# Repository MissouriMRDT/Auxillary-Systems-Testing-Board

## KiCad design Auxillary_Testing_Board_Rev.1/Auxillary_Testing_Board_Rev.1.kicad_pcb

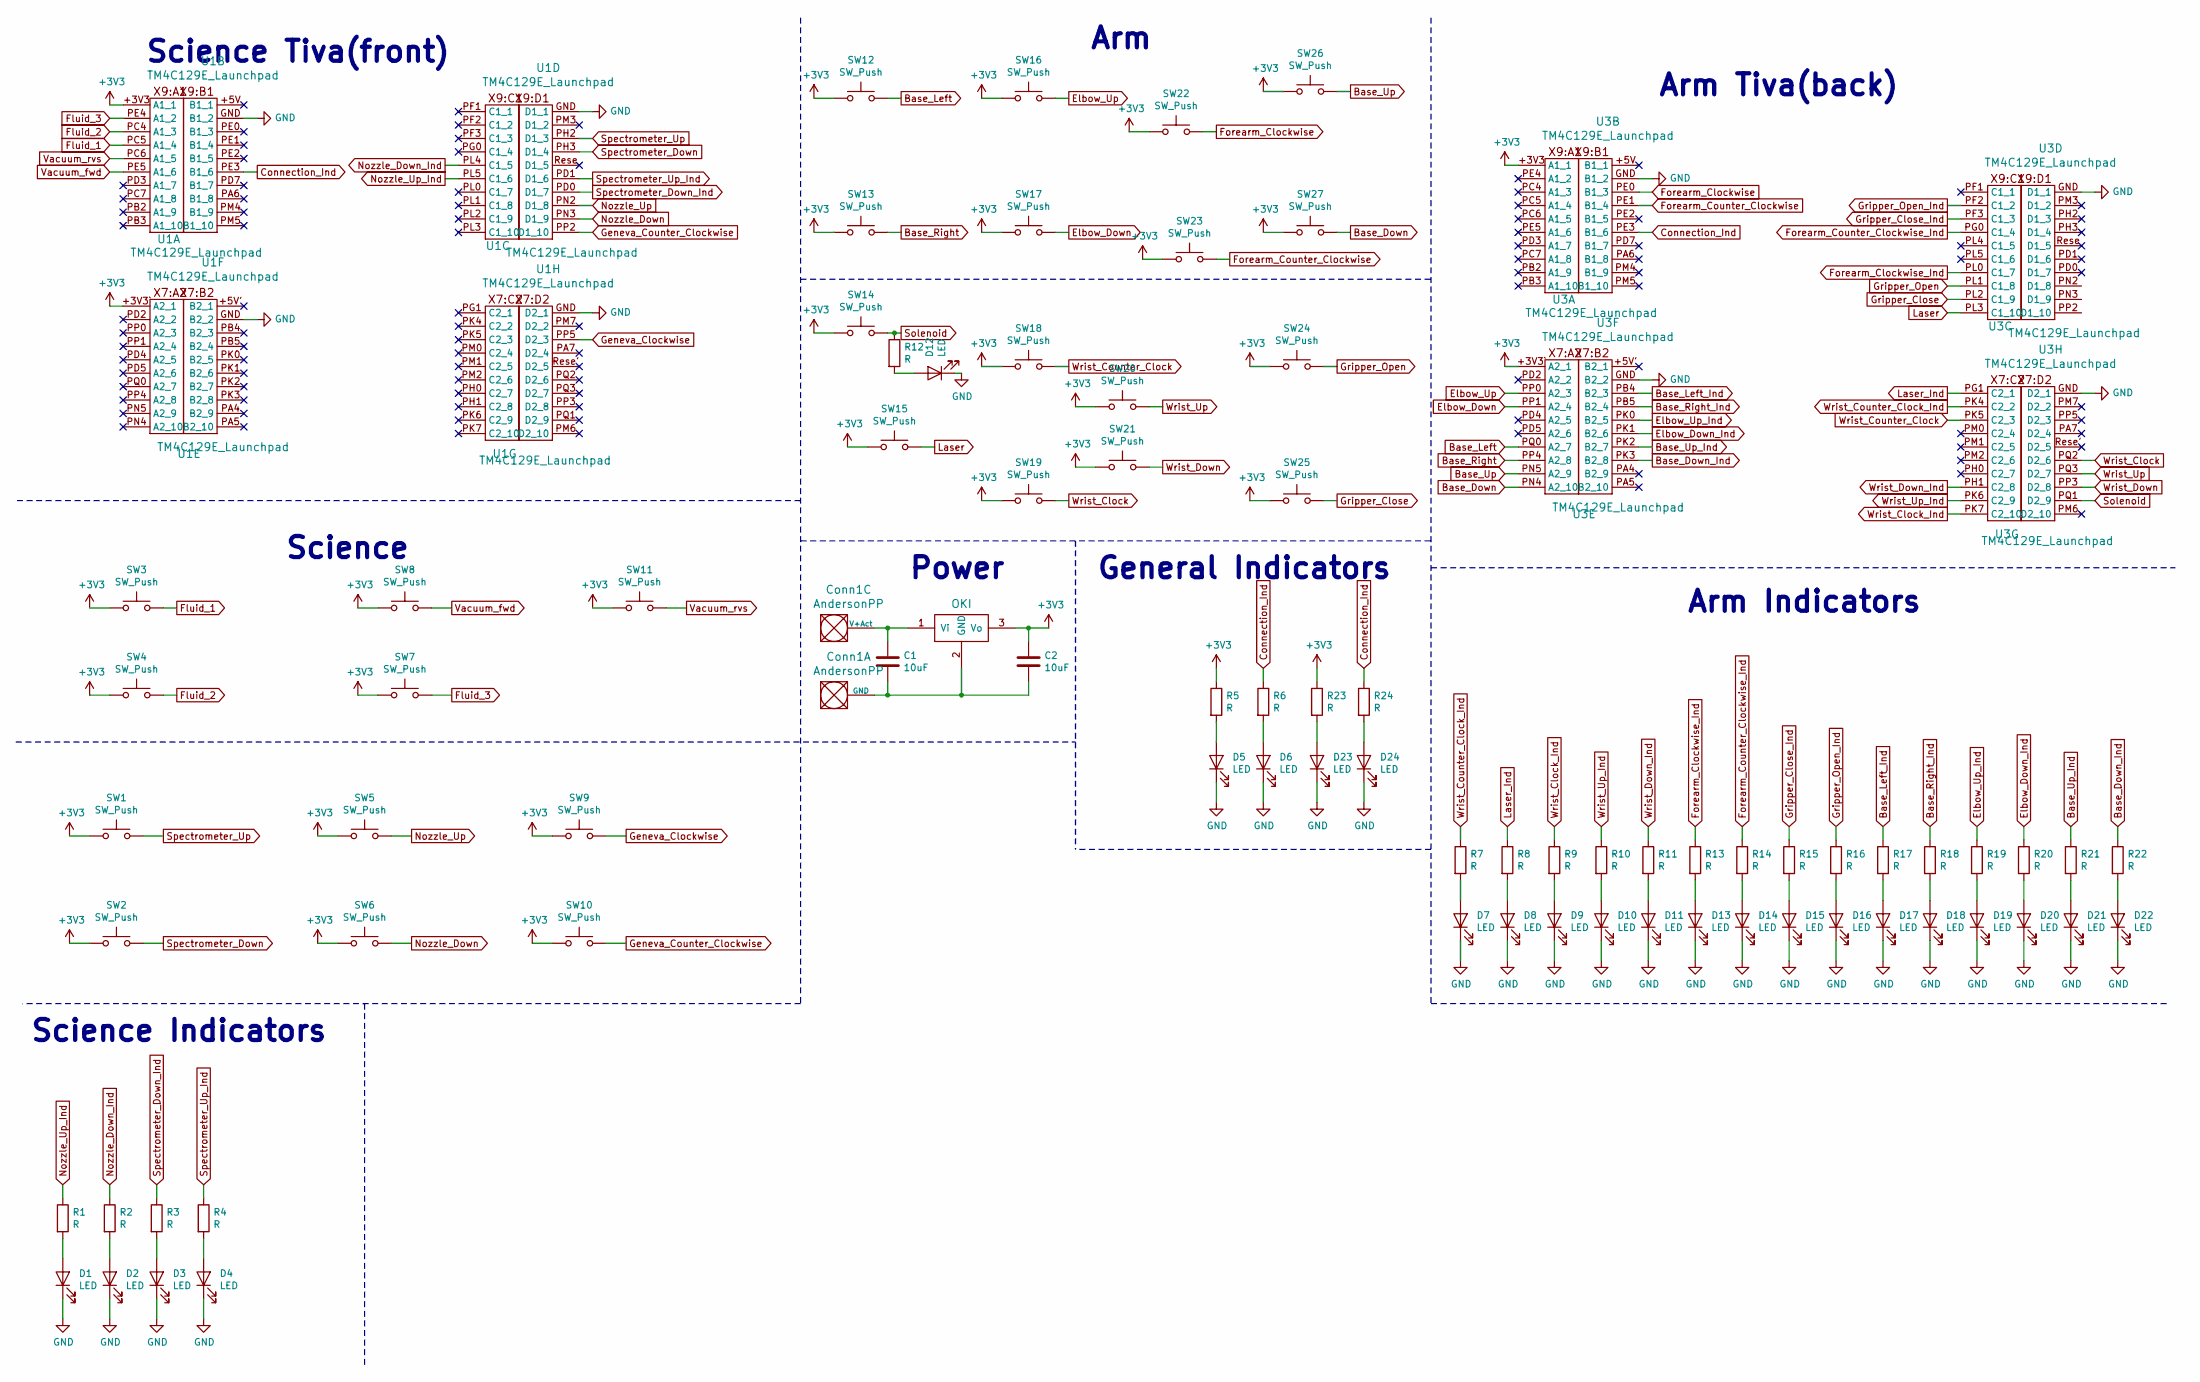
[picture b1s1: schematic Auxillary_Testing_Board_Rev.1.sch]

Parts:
C1, C2: 10uF; C_0603_1608Metric_Pad1.05x0.95mm_HandSolder
Conn1: AndersonPP; Anderson_2_Horizontal_Side_by_Side
D1, D2, D3, D4, D5, D6, D7, D8, D9, D10, D11, D12, D13, D14, D15, D16, D17, D18, D19, D20, D21, D22, D23, D24: LED; LED_0603_1608Metric_Pad1.05x0.95mm_HandSolder
R1, R2, R3, R4, R5, R6, R7, R8, R9, R10, R11, R12, R13, R14, R15, R16, R17, R18, R19, R20, R21, R22, R23, R24: R; R_0603_1608Metric_Pad1.05x0.95mm_HandSolder
SW1, SW2, SW3, SW4, SW5, SW6, SW7, SW8, SW9, SW10, SW11, SW12, SW13, SW14, SW15, SW16, SW17, SW18, SW19, SW20, SW21, SW22, SW23, SW24, SW25, SW26, SW27: SW_Push; SW_SPST_TL3305A
U1, U3: TM4C129E_Launchpad; Auxillary_Testing_Board
U2: OKI; OKI_Horizontal

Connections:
+3V3: C2.1, R5.1, R23.1, SW1.1, SW2.1, SW3.1, SW4.1, SW5.1, SW6.1, SW7.1, SW8.1, SW9.1, SW10.1, SW11.1, SW12.1, SW13.1, SW14.1, SW15.1, SW16.1, SW17.1, SW18.1, SW19.1, SW20.1, SW21.1, SW22.1, SW23.1, SW24.1, SW25.1, SW26.1, SW27.1, U1.+3V3 (A1_1), U1.+3V3', U1.+3V3` (A2_1), U2.3 (Vo), U3.+3V3 (A1_1), U3.+3V3` (A2_1)
Base_Down: SW27.2, U1.PN4 (A2_10), U3.PN4 (A2_10)
Base_Down_Ind: R22.1, U1.PK3 (B2_8), U3.PK3 (B2_8)
Base_Left: SW12.2, U1.PQ0 (A2_7), U3.PQ0 (A2_7)
Base_Left_Ind: R17.1, U1.PB4 (B2_3), U3.PB4 (B2_3)
Base_Right: SW13.2, U1.PP4 (A2_8), U3.PP4 (A2_8)
Base_Right_Ind: R18.1, U1.PB5 (B2_4), U3.PB5 (B2_4)
Base_Up: SW26.2, U1.PN5 (A2_9), U3.PN5 (A2_9)
Base_Up_Ind: R21.1, U1.PK2 (B2_7), U3.PK2 (B2_7)
Connection_Ind: R6.1, R24.1, U1.PE3 (B1_6), U3.PE3 (B1_6)
Elbow_Down: SW17.2, U1.PP1 (A2_4), U3.PP1 (A2_4)
Elbow_Down_Ind: R20.1, U1.PK1 (B2_6), U3.PK1 (B2_6)
Elbow_Up: SW16.2, U1.PP0 (A2_3), U3.PP0 (A2_3)
Elbow_Up_Ind: R19.1, U1.PK0 (B2_5), U3.PK0 (B2_5)
Fluid_1: SW3.2, U1.PC5 (A1_4)
Fluid_2: SW4.2, U1.PC4 (A1_3)
Fluid_3: SW7.2, U1.PE4 (A1_2)
Forearm_Clockwise: SW22.2, U1.PE0 (B1_3), U3.PE0 (B1_3)
Forearm_Clockwise_Ind: R13.1, U1.PL0 (C1_7), U3.PL0 (C1_7)
Forearm_Counter_Clockwise: SW23.2, U1.PE1 (B1_4), U3.PE1 (B1_4)
Forearm_Counter_Clockwise_Ind: R14.1, U1.PG0 (C1_4), U3.PG0 (C1_4)
Geneva_Clockwise: SW9.2, U1.PP5 (D2_3)
Geneva_Counter_Clockwise: SW10.2, U1.PP2 (D1_10)
Gripper_Close: SW25.2, U1.PL2 (C1_9), U3.PL2 (C1_9)
Gripper_Close_Ind: R15.1, U1.PF3 (C1_3), U3.PF3 (C1_3)
Gripper_Open: SW24.2, U1.PL1 (C1_8), U3.PL1 (C1_8)
Gripper_Open_Ind: R16.1, U1.PF2 (C1_2), U3.PF2 (C1_2)
Laser: SW15.2, U1.PL3 (C1_10), U3.PL3 (C1_10)
Laser_Ind: R8.1, U1.PG1 (C2_1), U3.PG1 (C2_1)
unnamed: C1.1, Conn1.2 (V+Log), Conn1.3 (V+Act), U2.1 (Vi)
unnamed: D1.2 (A), R1.2
unnamed: D2.2 (A), R2.2
unnamed: D3.2 (A), R3.2
unnamed: D4.2 (A), R4.2
unnamed: D5.2 (A), R5.2
unnamed: D6.2 (A), R6.2
unnamed: D7.2 (A), R7.2
unnamed: D8.2 (A), R8.2
unnamed: D9.2 (A), R9.2
unnamed: D10.2 (A), R10.2
unnamed: D11.2 (A), R11.2
unnamed: D12.2 (A), R12.2
unnamed: D13.2 (A), R13.2
unnamed: D14.2 (A), R14.2
unnamed: D15.2 (A), R15.2
unnamed: D16.2 (A), R16.2
unnamed: D17.2 (A), R17.2
unnamed: D18.2 (A), R18.2
unnamed: D19.2 (A), R19.2
unnamed: D20.2 (A), R20.2
unnamed: D21.2 (A), R21.2
unnamed: D22.2 (A), R22.2
unnamed: D23.2 (A), R23.2
unnamed: D24.2 (A), R24.2
Nozzle_Down: SW6.2, U1.PN3 (D1_9)
Nozzle_Down_Ind: R2.1, U1.PL4 (C1_5)
Nozzle_Up: SW5.2, U1.PN2 (D1_8)
Nozzle_Up_Ind: R1.1, U1.PL5 (C1_6)
Solenoid: R12.1, SW14.2, U1.PQ1 (D2_9), U3.PQ1 (D2_9)
Spectrometer_Down: SW2.2, U1.PH3 (D1_4)
Spectrometer_Down_Ind: R3.1, U1.PD0 (D1_7)
Spectrometer_Up: SW1.2, U1.PH2 (D1_3)
Spectrometer_Up_Ind: R4.1, U1.PD1 (D1_6)
Vacuum_fwd: SW8.2, U1.PE5 (A1_6)
Vacuum_rvs: SW11.2, U1.PC6 (A1_5)
Wrist_Clock: SW19.2, U1.PQ2 (D2_6), U3.PQ2 (D2_6)
Wrist_Clock_Ind: R9.1, U1.PK7 (C2_10), U3.PK7 (C2_10)
Wrist_Counter_Clock: SW18.2, U1.PK5 (C2_3), U3.PK5 (C2_3)
Wrist_Counter_Clock_Ind: R7.1, U1.PK4 (C2_2), U3.PK4 (C2_2)
Wrist_Down: SW21.2, U1.PP3 (D2_8), U3.PP3 (D2_8)
Wrist_Down_Ind: R11.1, U1.PH1 (C2_8), U3.PH1 (C2_8)
Wrist_Up: SW20.2, U1.PQ3 (D2_7), U3.PQ3 (D2_7)
Wrist_Up_Ind: R10.1, U1.PK6 (C2_9), U3.PK6 (C2_9)

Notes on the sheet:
Arm
Science
Power
Science Tiva(front)
Arm Tiva(back)
Arm Indicators
Science Indicators
General Indicators

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
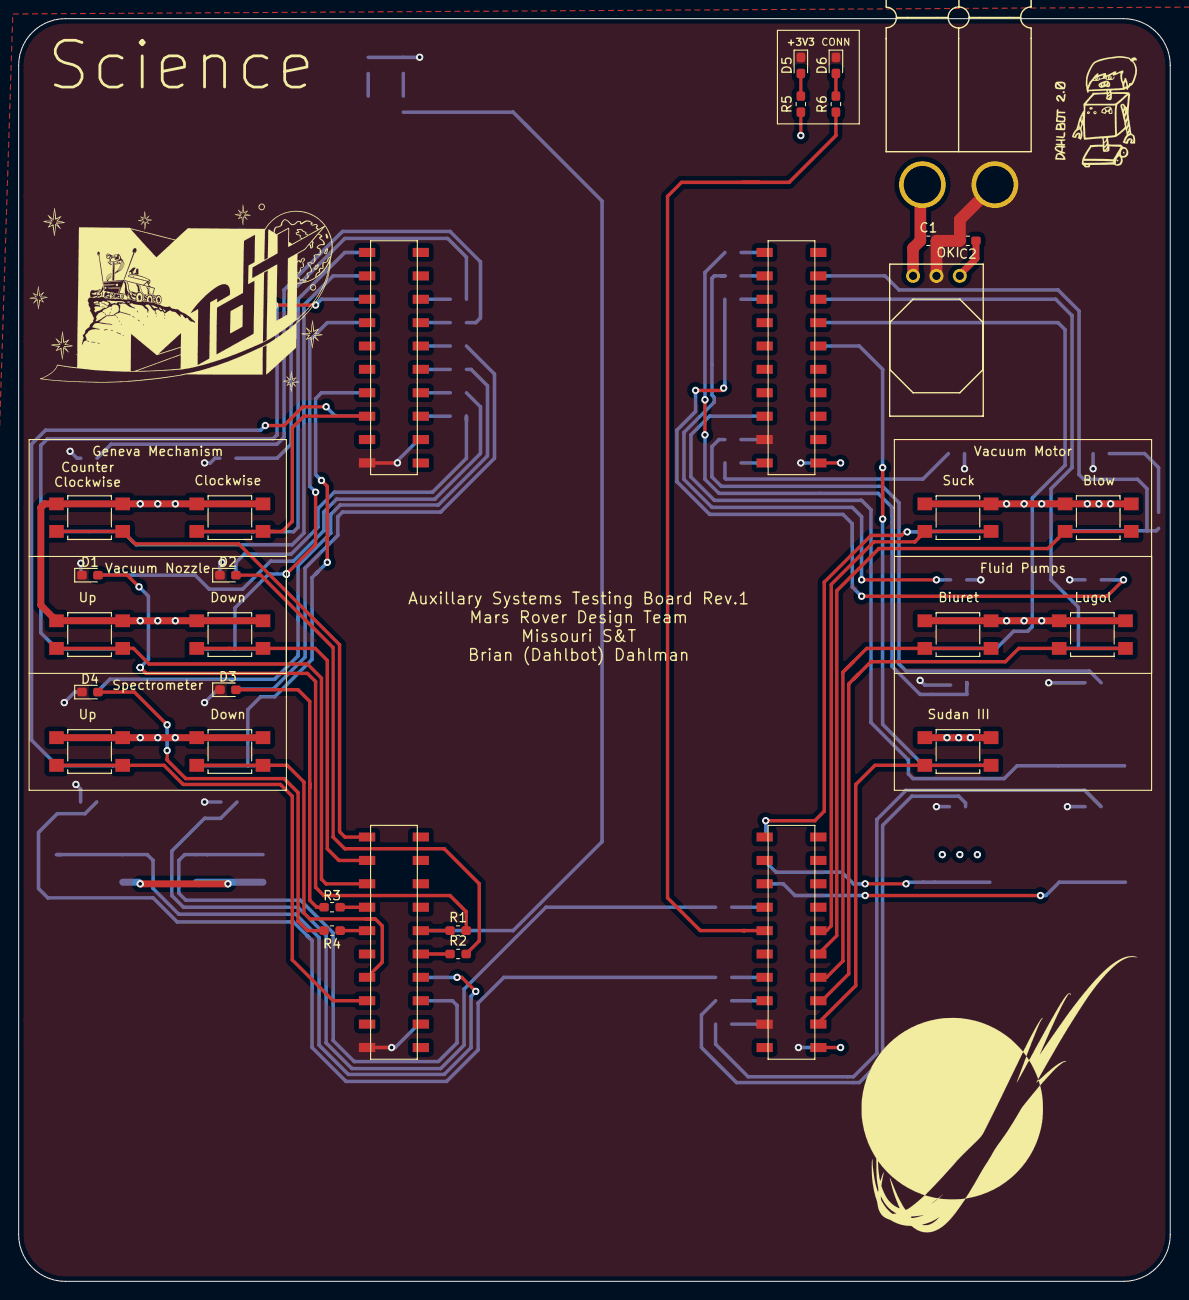
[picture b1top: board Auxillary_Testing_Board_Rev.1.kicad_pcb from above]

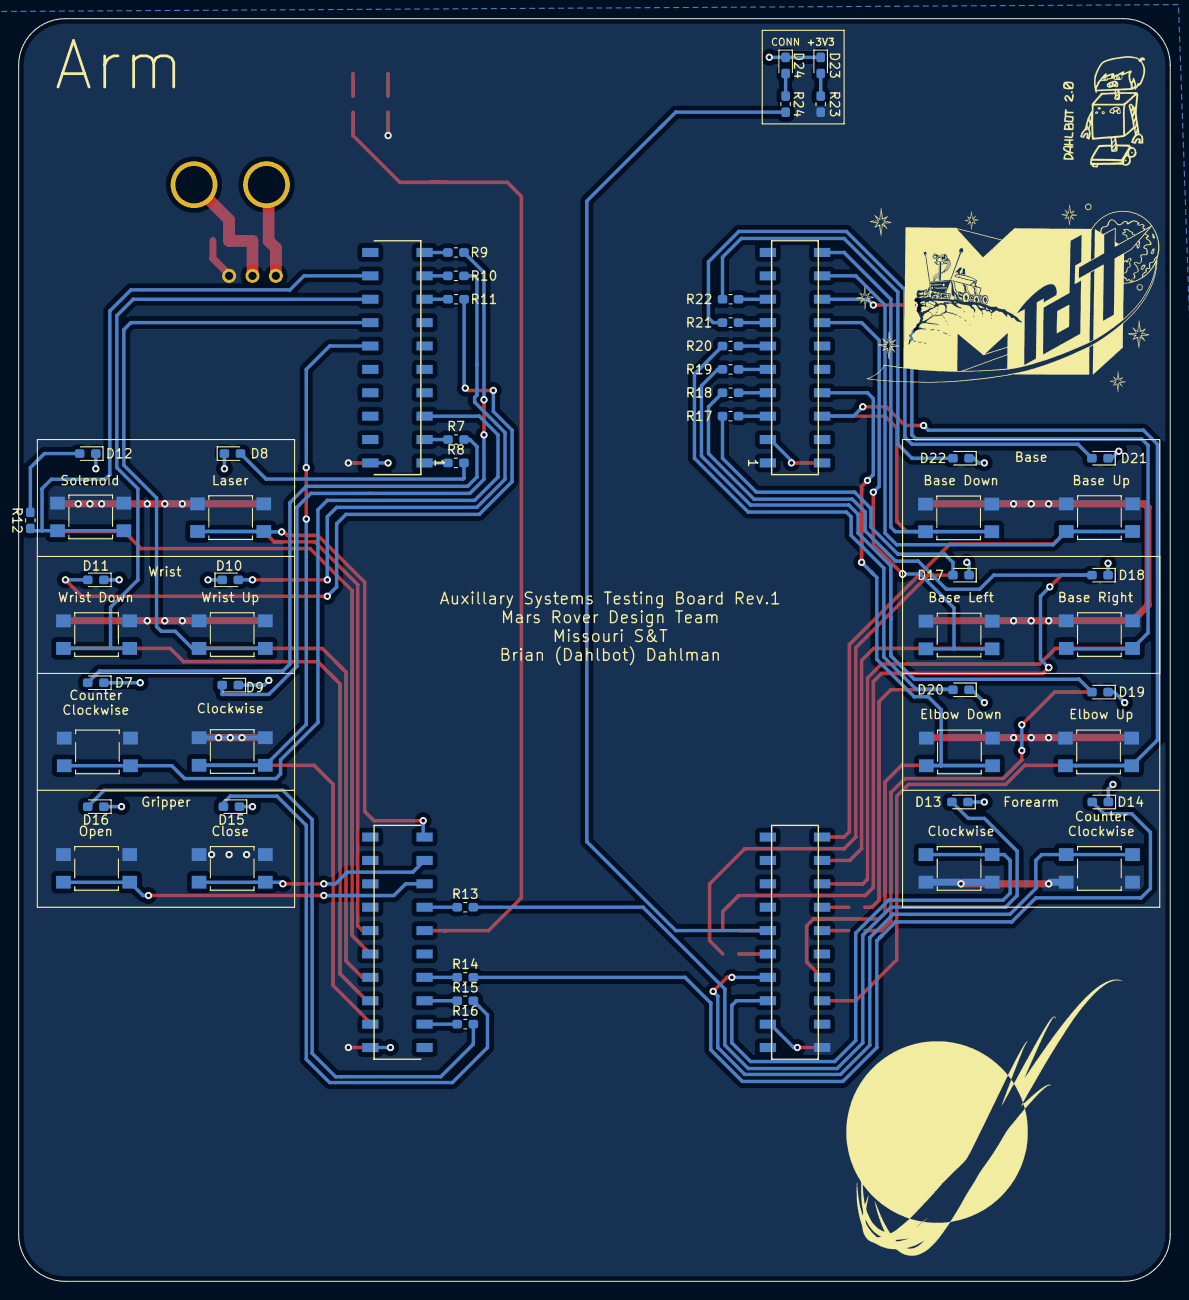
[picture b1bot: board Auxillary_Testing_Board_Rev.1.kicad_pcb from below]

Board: 2 copper layers, 125.1 x 137.2 mm, 80 parts (52 on the bottom side), 74 nets.

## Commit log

2019-10-05 created project
2019-10-05 schematic done ish
    needs footprints assigned
2019-10-05 finished layout maybe
2019-10-07 Added LEDs to the schematic
2019-10-26 layout routed, just need to make it look good
